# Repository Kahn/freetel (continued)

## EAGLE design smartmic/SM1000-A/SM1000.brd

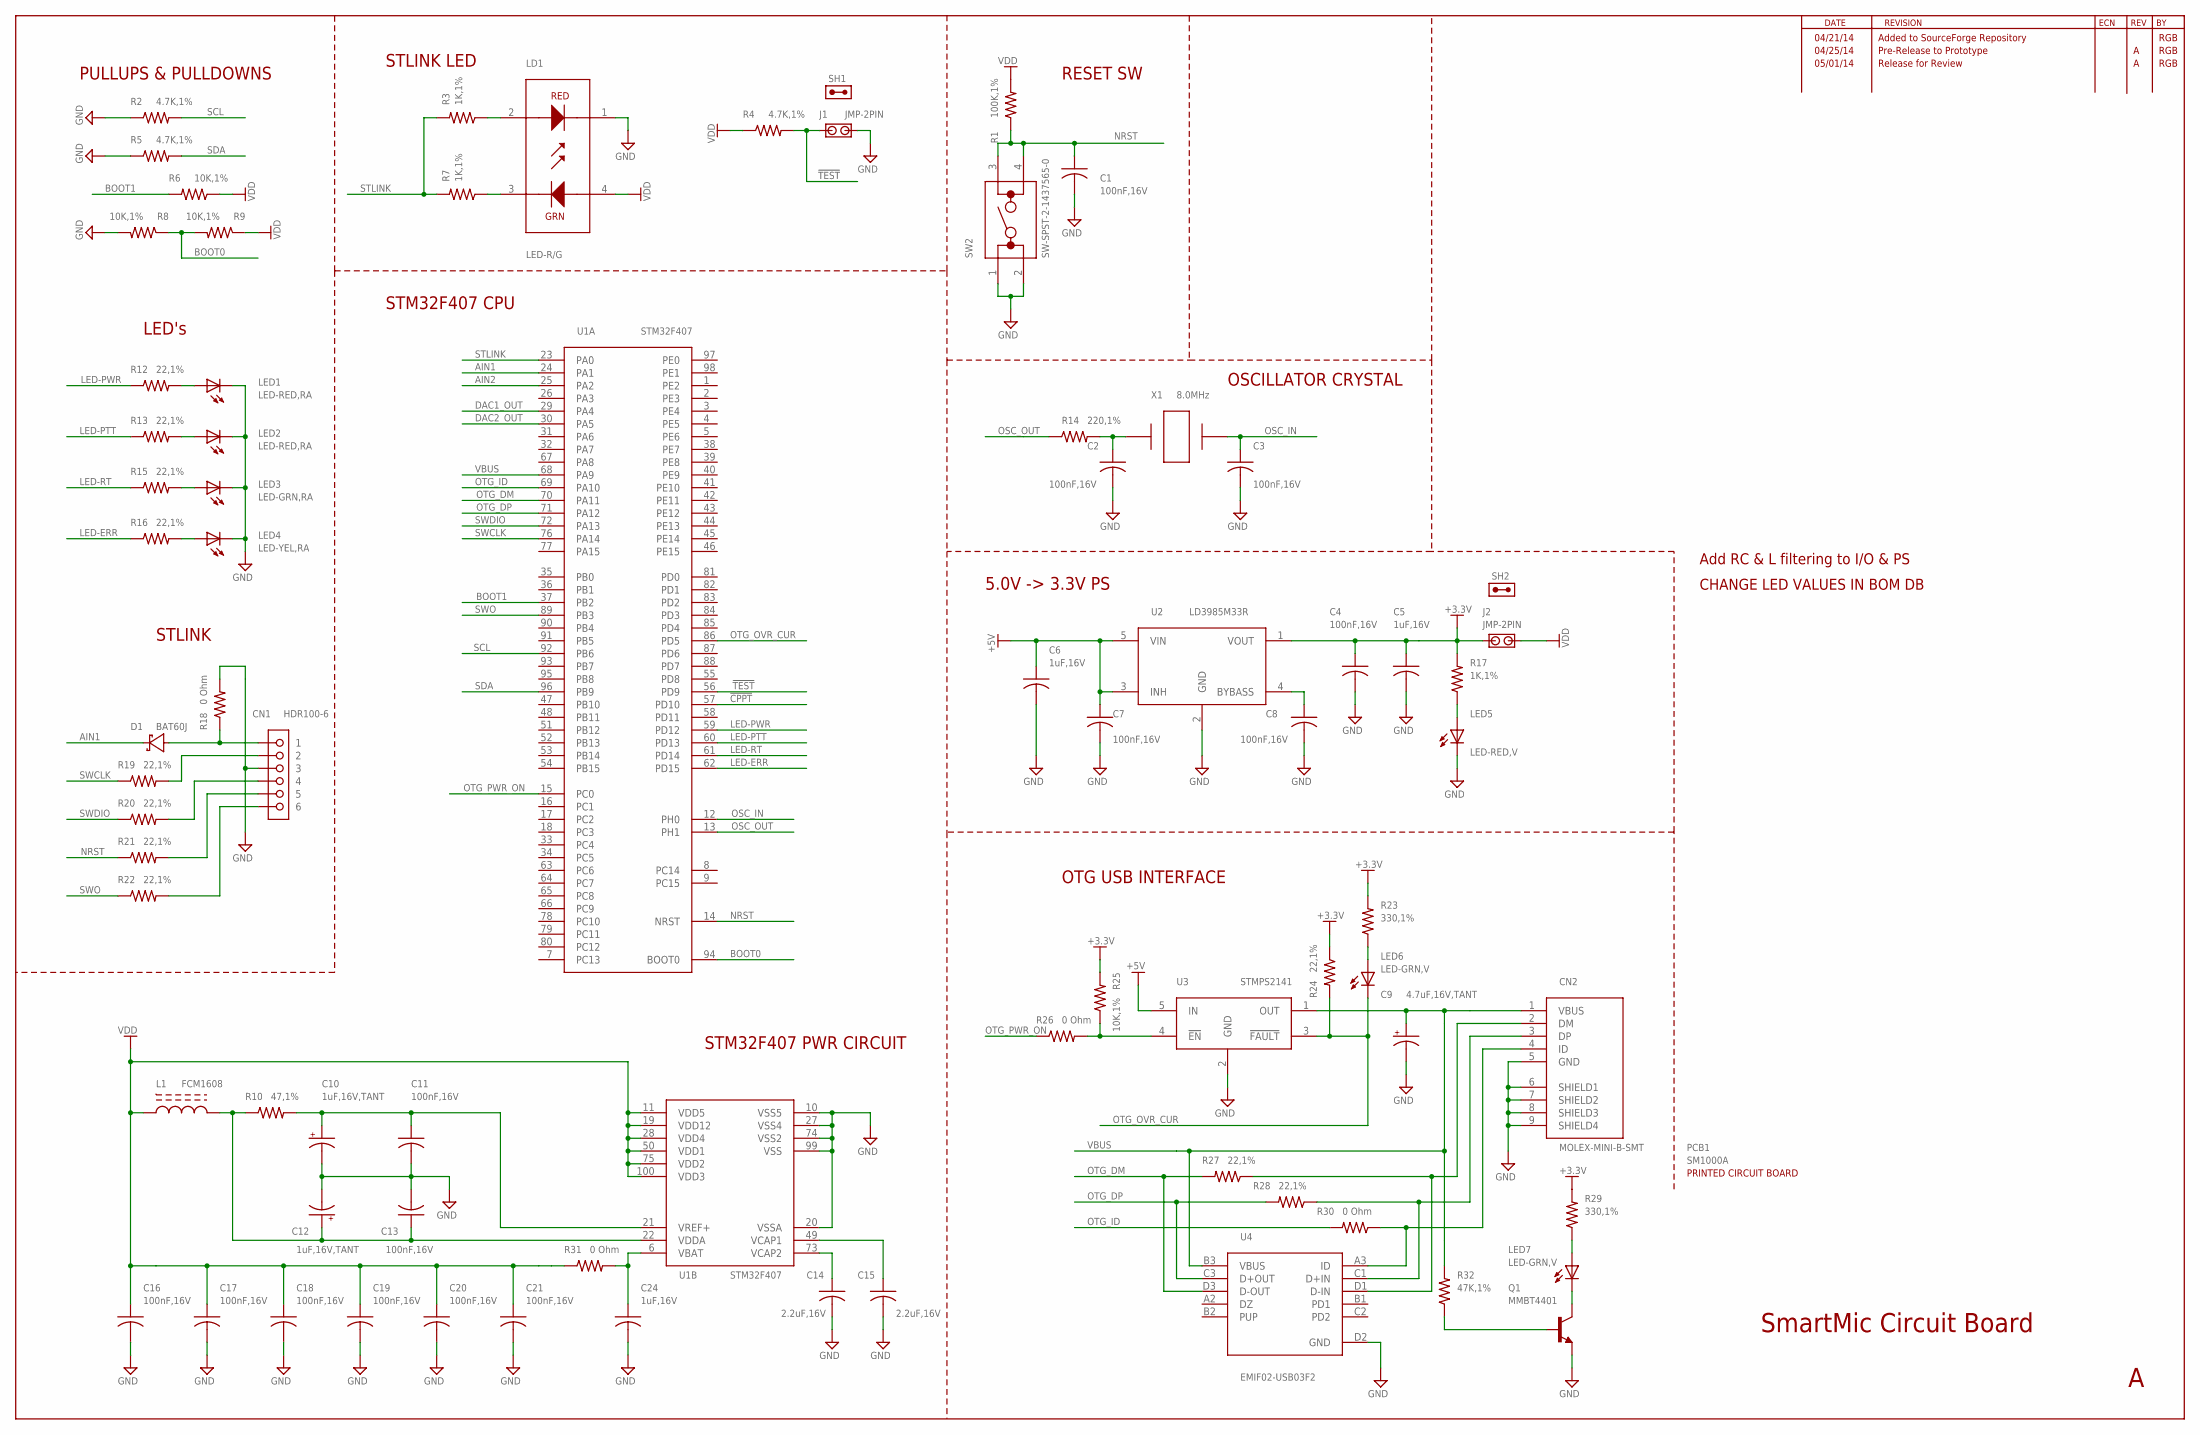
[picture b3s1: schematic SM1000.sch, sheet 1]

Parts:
C1, C2, C3, C4, C7, C8, C11, C13, C16, C17, C18, C19, C20, C21: 100nF,16V; C0603
C5, C6, C24: 1uF,16V; C0603
C9: 4.7uF,16V,TANT; C1206-TANT
C10, C12: 1uF,16V,TANT; C1206-TANT
C14, C15: 2.2uF,16V; C0805
CN1: HDR100-6
CN2: MOLEX-MINI-B-SMT
D1: BAT60J; SOD323R_INFINEON
J1, J2: JMP-2PIN; JMPR-2PIN
L1: FCM1608
LD1: LED-R/G
LED1, LED2: LED-RED,RA; LTST-S2200K
LED3: LED-GRN,RA; LTST-S2200K
LED4: LED-YEL,RA; LTST-S2200K
LED5: LED-RED,V; CHIP-LED-0603
LED6, LED7: LED-GRN,V; CHIP-LED-0603
PCB1: SM1000A; NOPACKAGE
Q1: MMBT4401; SOT23
R1: 100K,1%; R0603
R2, R4, R5: 4.7K,1%; R0603
R3, R7, R17: 1K,1%; R0603
R6, R8, R9, R25: 10K,1%; R0603
R10: 47,1%; R0603
R12, R13, R15, R16, R19, R20, R21, R22, R24, R27, R28: 22,1%; R0603
R14: 220,1%; R0603
R18, R26, R30, R31: 0 Ohm; R0603
R23, R29: 330,1%; R0603
R32: 47K,1%; R0603
SH1, SH2: SHUNT,0.1IN; NOPACKAGE
SW2: SW-SPST-2-1437565-0; SW-SPST-TE-2-1437565-0
U1: STM32F407; LQFP100-14
U2: LD3985M33R; SOT23-5L
U3: STMPS2141; SOT23-5L
U4: EMIF02-USB03F2; ECOPACK-11
X1: 8.0MHz; HC49-SMT

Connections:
!CPPT!: U1.57 (PD10); also elsewhere on the board
!TEST!: J1.1, R4.2, U1.56 (PD9)
+3.3V: C4.1, C5.1, J2.1, R17.2, R23.2, R24.1, R25.2, R29.2, U2.1 (VOUT)
+5V: C6.1, C7.1, U2.3 (INH), U2.5 (VIN), U3.5 (IN); also elsewhere on the board
AIN1: D1.C, U1.24 (PA1)
AIN2: U1.25 (PA2); also elsewhere on the board
BOOT0: R8.1, R9.2, U1.94 (BOOT0)
BOOT1: R6.2, U1.37 (PB2)
DAC1_OUT: U1.29 (PA4); also elsewhere on the board
DAC2_OUT: U1.30 (PA5); also elsewhere on the board
GND: C1.2, C2.2, C3.2, C4.2, C5.2, C6.2, C7.2, C8.2, C9.2, C10.2, C11.2, C12.2, C13.2, C14.2, C15.2, C16.2, C17.2, C18.2, C19.2, C20.2, C21.2, C24.2, CN1.3, CN2.5 (GND), CN2.6 (SHIELD1), CN2.7 (SHIELD2), CN2.8 (SHIELD3), CN2.9 (SHIELD4), J1.2, LD1.1, LED1.C, LED2.C, LED3.C, LED4.C, LED5.C, Q1.2 (E), R2.1, R5.1, R8.2, R18.2, SW2.1, SW2.2, U1.10 (VSS5), U1.20 (VSSA), U1.27 (VSS4), U1.74 (VSS2), U1.99 (VSS), U2.2 (GND), U3.2 (GND), U4.D2 (GND); also elsewhere on the board
LED-ERR: R16.1, U1.62 (PD15)
LED-PTT: R13.1, U1.60 (PD13)
LED-PWR: R12.1, U1.59 (PD12)
LED-RT: R15.1, U1.61 (PD14)
unnamed: C14.1, U1.73 (VCAP2)
unnamed: C24.1, R31.2, U1.6 (VBAT)
unnamed: C15.1, U1.49 (VCAP1)
unnamed: C10.1, C11.1, R10.2, U1.21 (VREF+)
unnamed: C12.1, C13.1, L1.2, R10.1, U1.22 (VDDA)
unnamed: CN1.1, D1.A, R18.1
unnamed: CN1.2, R19.2
unnamed: CN1.4, R20.2
unnamed: CN1.5, R21.2
unnamed: C2.1, R14.2, X1.1
unnamed: CN1.6, R22.2
unnamed: C8.1, U2.4 (BYBASS)
unnamed: LD1.2, R3.1
unnamed: LD1.3, R7.1
unnamed: Q1.1 (B), R32.1
unnamed: LED1.A, R12.2
unnamed: LED2.A, R13.2
unnamed: LED3.A, R15.2
unnamed: LED5.A, R17.1
unnamed: LED4.A, R16.2
unnamed: CN2.3 (DP), R28.1, U4.C1 (D+IN)
unnamed: CN2.2 (DM), R27.1, U4.D1 (D-IN)
unnamed: LED7.C, Q1.3 (C)
unnamed: LED7.A, R29.1
unnamed: CN2.4 (ID), R30.1, U4.A3 (ID)
unnamed: LED6.A, R23.1
unnamed: R25.1, R26.2, U3.4 (!EN!)
NRST: C1.1, R1.1, R21.1, SW2.3, SW2.4, U1.14 (NRST)
OSC_IN: C3.1, U1.12 (PH0), X1.2
OSC_OUT: R14.1, U1.13 (PH1)
OTG_DM: R27.2, U1.70 (PA11), U4.D3 (D-OUT)
OTG_DP: R28.2, U1.71 (PA12), U4.C3 (D+OUT)
OTG_ID: R30.2, U1.69 (PA10)
OTG_OVR_CUR: LED6.C, R24.2, U1.86 (PD5), U3.3 (!FAULT!)
OTG_PWR_ON: R26.1, U1.15 (PC0)
SCL: R2.2, U1.92 (PB6)
SDA: R5.2, U1.96 (PB9)
STLINK: R3.2, R7.2, U1.23 (PA0)
SWCLK: R19.1, U1.76 (PA14)
SWDIO: R20.1, U1.72 (PA13)
SWO: R22.1, U1.89 (PB3)
VBUS: C9.1, CN2.1 (VBUS), R32.2, U1.68 (PA9), U3.1 (OUT), U4.B3 (VBUS)
VDD: C16.1, C17.1, C18.1, C19.1, C20.1, C21.1, J2.2, L1.1, LD1.4, R1.2, R4.1, R6.1, R9.1, R31.1, U1.11 (VDD5), U1.19 (VDD12), U1.28 (VDD4), U1.50 (VDD1), U1.75 (VDD2), U1.100 (VDD3); also elsewhere on the board

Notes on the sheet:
PULLUPS & PULLDOWNS
LED's
STLINK
STLINK LED
RESET SW
OSCILLATOR CRYSTAL
5.0V -> 3.3V PS
OTG USB INTERFACE
STM32F407 CPU
STM32F407 PWR CIRCUIT
SmartMic Circuit Board
04/21/14
Added to SourceForge Repository
RGB
CHANGE LED VALUES IN BOM DB
Add RC & L filtering to I/O & PS
04/25/14
Pre-Release to Prototype
05/01/14
Release for Review

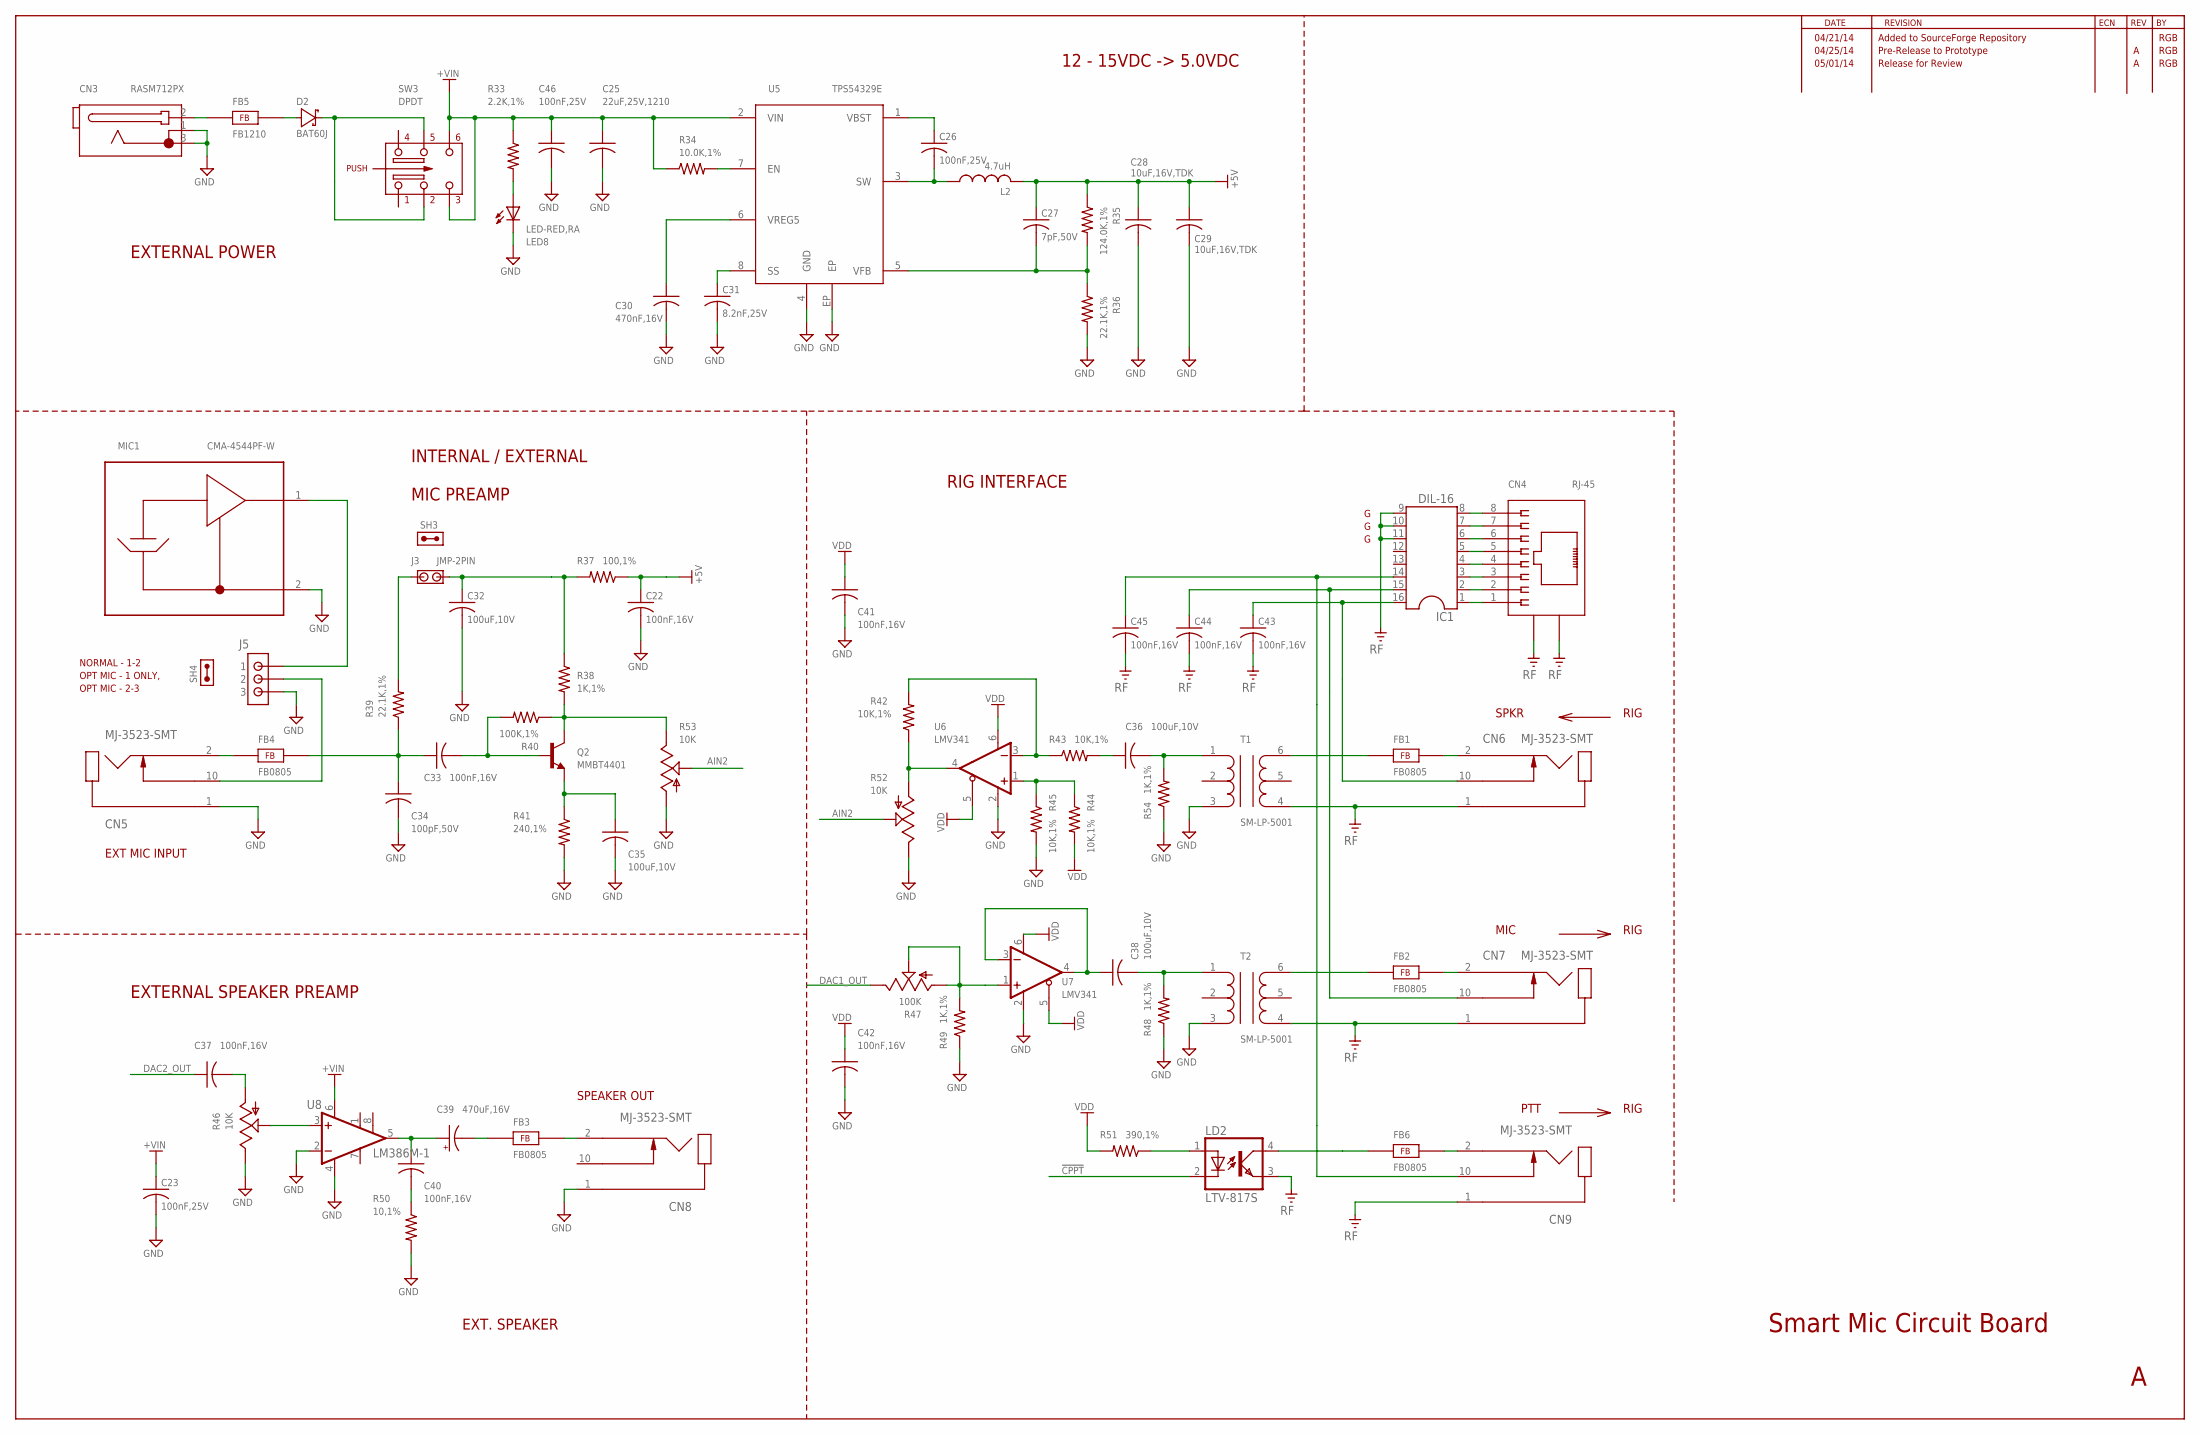
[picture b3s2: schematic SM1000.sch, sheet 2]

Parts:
C22, C33, C37, C40, C41, C42, C43, C44, C45: 100nF,16V; C0603
C23, C26, C46: 100nF,25V; C0603
C25: 22uF,25V,1210; C1210
C27: 7pF,50V; C0603
C28, C29: 10uF,16V,TDK; C1206
C30: 470nF,16V; C0603
C31: 8.2nF,25V; C0603
C32, C35, C36, C38: 100uF,10V; C1210
C34: 100pF,50V; C0603
C39: 470uF,16V; CAP-CHEMI-HA0
CN3: RASM712PX
CN4: RJ-45; CONN-RJ45-MOLEX-44144-003
CN5, CN6, CN7, CN8, CN9: MJ-3523-SMT
D2: BAT60J; SOD323R_INFINEON
FB1, FB2, FB3, FB4, FB6: FB0805; FE0805
FB5: FB1210; FE1210
IC1: DIL-16; SOCKET-16
J3: JMP-2PIN; JMPR-2PIN
J5: JMPR-3PIN
L2: 4.7uH; SRN6045
LD2: LTV-817S; SMD4
LED8: LED-RED,RA; LTST-S2200K
MIC1: CMA-4544PF-W
Q2: MMBT4401; SOT23
R33: 2.2K,1%; R0603
R34: 10.0K,1%; R0603
R35: 124.0K,1%; R0603
R36, R39: 22.1K,1%; R0603
R37: 100,1%; R0603
R38, R48, R49, R54: 1K,1%; R0603
R40: 100K,1%; R0603
R41: 240,1%; R0603
R42, R43, R44, R45: 10K,1%; R0603
R46: 10K; POT-3310C
R47: 100K; TRIMPOT91
R50: 10,1%; R0603
R51: 390,1%; R0603
R52, R53: 10K; TRIMPOT91
SH3, SH4: SHUNT,0.1IN; NOPACKAGE
SW3: DPDT; SW-PWR
T1, T2: SM-LP-5001
U5: TPS54329E; PSO-DDA
U6, U7: LMV341; SOT23-6
U8: LM386M-1; SO08

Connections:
!CPPT!: LD2.2 (C); also elsewhere on the board
+5V: C22.1, C27.1, C28.1, C29.1, L2.2, R35.1, R37.1; also elsewhere on the board
+VIN: C23.1, C25.1, C46.1, R33.1, R34.1, SW3.3, SW3.6, U5.2 (VIN), U8.6 (VS)
AIN2: R52.2, R53.2; also elsewhere on the board
DAC1_OUT: R47.1; also elsewhere on the board
DAC2_OUT: C37.1; also elsewhere on the board
GND: C22.2, C23.2, C25.2, C28.2, C29.2, C30.2, C31.2, C32.2, C34.2, C35.2, C41.2, C42.2, C46.2, CN3.1, CN3.3, CN5.1, CN8.1, J5.3, LED8.C, MIC1.2, R36.2, R41.2, R45.2, R46.1, R48.1, R49.1, R50.2, R52.1, R53.3, R54.1, T1.3, T2.3, U5.4 (GND), U5.EP, U6.2 (GND), U7.2 (GND), U8.2 (-IN), U8.4 (GND); also elsewhere on the board
MIC: C44.1, CN7.10, IC1.15
unnamed: C26.1, U5.1 (VBST)
unnamed: D2.A, FB5.2
unnamed: C33.1, C34.1, FB4.2, R39.1
unnamed: C27.2, R35.2, R36.1, U5.5 (VFB)
unnamed: J5.1, MIC1.1
unnamed: FB1.1, T1.6
unnamed: C37.2, R46.3
unnamed: C33.2, Q2.1 (B), R40.2
unnamed: C39.1, C40.1, U8.5 (OUT)
unnamed: C31.1, U5.8 (SS)
unnamed: R46.2, U8.3 (+IN)
unnamed: C30.1, U5.6 (VREG5)
unnamed: C35.1, Q2.2 (E), R41.1
unnamed: R34.2, U5.7 (EN)
unnamed: C40.2, R50.1
unnamed: C39.2, FB3.1
unnamed: J3.1, R39.2
unnamed: C32.1, J3.2, R37.2, R38.1
unnamed: LED8.A, R33.2
unnamed: R42.1, R52.3, U6.4 (OUT)
unnamed: LD2.1 (A), R51.1
unnamed: C36.1, R43.2
unnamed: CN4.8, IC1.8
unnamed: CN4.7, IC1.7
unnamed: CN4.6, IC1.6
unnamed: CN4.5, IC1.5
unnamed: CN4.4, IC1.4
unnamed: CN4.3, IC1.3
unnamed: CN4.2, IC1.2
unnamed: CN4.1, IC1.1
unnamed: R44.1, R45.1, U6.1 (+IN)
unnamed: CN5.10, J5.2
unnamed: FB2.1, T2.6
unnamed: R42.2, R43.1, U6.3 (-IN)
unnamed: C36.2, R54.2, T1.1
unnamed: CN6.2, FB1.2
unnamed: C38.2, R48.2, T2.1
unnamed: Q2.3 (C), R38.2, R40.1, R53.1
unnamed: C38.1, U7.3 (-IN), U7.4 (OUT)
unnamed: CN7.2, FB2.2
unnamed: CN9.2, FB6.2
unnamed: FB6.1, LD2.4 (COL)
unnamed: CN8.2, FB3.2
unnamed: CN5.2, FB4.1
unnamed: CN3.2, FB5.1
unnamed: D2.C, SW3.2, SW3.5
unnamed: R47.2, R47.3, R49.2, U7.1 (+IN)
PTT: C45.1, CN9.10, IC1.14
RF: C43.2, C44.2, C45.2, CN4.9, CN4.10, CN6.1, CN7.1, CN9.1, IC1.9, IC1.10, IC1.11, LD2.3 (EMIT), T1.4, T2.4
SPKR: C43.1, CN6.10, IC1.16
SW: C26.2, L2.1, U5.3 (SW)
VDD: C41.1, C42.1, R44.2, R51.2, U6.5 (!SHDN!), U6.6 (V+), U7.5 (!SHDN!), U7.6 (V+); also elsewhere on the board

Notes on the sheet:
SPKR
MIC
RIG
SPEAKER OUT
PTT
EXT MIC INPUT
EXTERNAL POWER
12 - 15VDC -> 5.0VDC
INTERNAL / EXTERNAL
MIC PREAMP
EXTERNAL SPEAKER PREAMP
RIG INTERFACE
Smart Mic Circuit Board
EXT. SPEAKER
NORMAL - 1-2
OPT MIC - 1 ONLY,
OPT MIC - 2-3
04/25/14
Pre-Release to Prototype
RGB
04/21/14
Added to SourceForge Repository
05/01/14
Release for Review

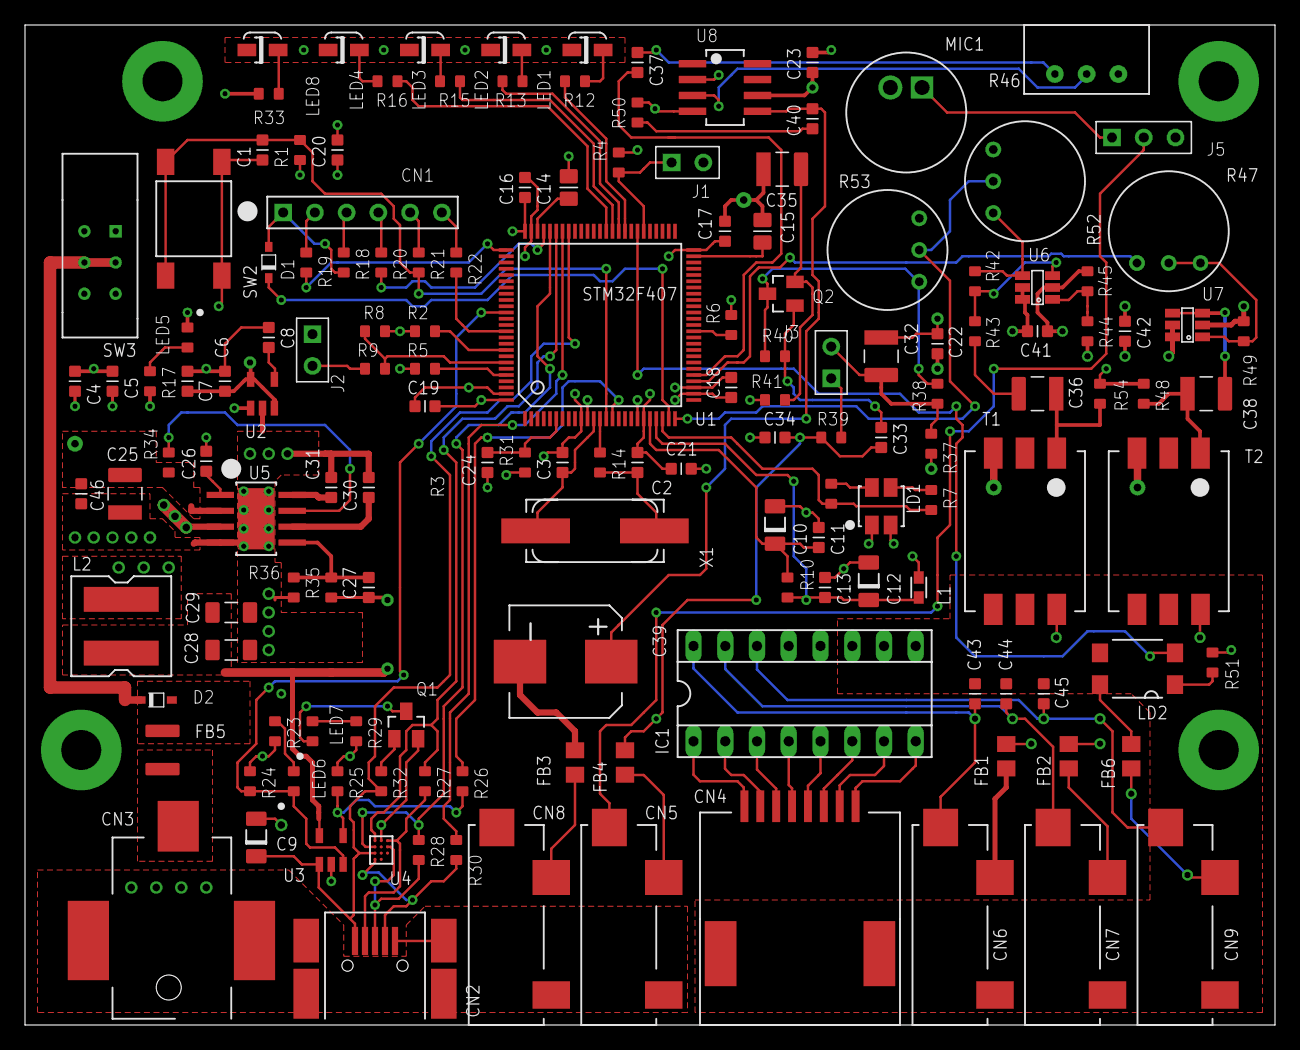
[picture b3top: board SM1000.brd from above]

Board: 4 copper layers, 100.0 x 80.0 mm, 155 parts (0 on the bottom side), 111 nets.

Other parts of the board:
DRILEGEND: DRILEGEND

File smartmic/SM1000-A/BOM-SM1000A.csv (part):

"Bill of Materials from SM1000.sch, 154 parts, grouped by values, as of 5/1/2014 3:17:26 PM"
"Part","Qty","DEFINITION","MANUFACTURER","MFG_NUMBER","DISTRIBUTOR","DIST_NUMBER","GENERIC","ROHS","COST100",
"C1, C2, C3, C4, C7, C8, C11, C13, C16, C17, C18, C19, C20, C21, C22, C33, C37, C40, C41, C42, C43, C44, C45","23","CAP CER 0.1UF 16V 10% X7R 0603","YAGEO","CC0603KRX7R7BB104","DIGIKEY","311-1088-1-ND","Y","Y","0.013"
"C5, C6, C24","3","CAP CER 1UF 16V 10% X5R 0603","TDK","C1608X5R1C105K080AA","DIGIKEY","445-1416-1-ND","Y","Y","0.034"
"C9","1","CAP TANT 4.7UF 16V 10% 1206","AVX","TAJA475K016RNJ","DIGIKEY","478-3868-1-ND","Y","Y","0.260"
"C10, C12","2","CAP TANT 1UF 16V 20% 1206","NICHICON","F931C105MAA","DIGIKEY","493-2364-1-ND","Y","Y","0.152"
"C14, C15","2","CAP CER 2.2UF 16V Y5V 0805","YAGEO","CC0805ZRY5V7BB225","DIGIKEY","311-1463-1-ND","Y","Y","0.042"
"C23, C26, C46","3","CAP CER 0.1UF 16V 10% X7R 0603","YAGEO","CC0603KRX7R7BB104","DIGIKEY","311-1088-1-ND","Y","Y","0.013"
"C25","1","CAP CER 22UF 25V 10% X5R 1210","MURATA","GRM32ER61E226KE15L","DIGIKEY","490-3889-1-ND","N","Y","0.540"
"C27","1","CAP CER 7PF 50V NPO 0603","YAGEO","CC0603DRNPO9BN7R0","DIGIKEY","311-1056-1-ND","N","Y","0.029"
"C28, C29","2","CAP CER 10UF 10V 20% X5R 1206","TDK","C3216X5R1A106M160AB","DIGIKEY","445-1387-1-ND","N","Y","0.114"
"C30","1","CAP CER 0.47UF 16V 10% X5R 0603","TDK","C1608X5R1C474K080AA","DIGIKEY","445-5152-1-ND","N","Y","0.030"
"C31","1","CAP CER 0.082UF 25V 10% X7R 0603","MURATA","GRM188R71E823KA01D","DIGIKEY","490-6434-1-ND","N","Y","0.050"
"C32, C35, C36, C38","4","CAP CER 100UF 10V 20% X5R 1210","SAMSUNG","CL32A107MPVNNNE","DIGIKEY","1276-3364-1-ND","Y","Y","0.735"
"C34","1","CAP CER 100PF 50V 5% NP0 0603","TDK","C1608NP01H101J080AA","DIGIKEY","445-14054-1-ND","Y","Y","0.038"
"C39","1","CAP ALUM 470UF 16V 20% SMD","UNITED CHEMI-CON","EMVE160ADA471MHA0G","DIGIKEY","565-2208-1-ND","Y","Y","0.456"
"CN1","1","CONN HEADER 6POS .100 VERT GOLD","MOLEX","22-10-2061","DIGIKEY","WM2726-ND","Y","Y","0.985"
"CN2","1","CONN RECEPT MINIUSB R/A 5POS SMD","MOLEX","0675031020","DIGIKEY","WM5461CT-ND","N","Y","0.856"
"CN3","1","CONN JACK R/A .100" PIN SMD","SWITCHCRAFT","RASM712PX","DIGIKEY","RASM712PX-ND","N","Y","1.082"
"CN4","1","CONN MOD JACK R/A 8P8C","MOLEX","0441440003","DIGIKEY","WM4595CT-ND","N","Y","1.387"
"CN5, CN6, CN7, CN8, CN9","5","CONN AUDIO JACK MONO 3.5MM SMD","CUI","MJ-3523-SMT-TR","DIGIKEY","CP-3523MJTR-ND","N","Y","0.796"
"D1, D2","2","DIODE SCHOTTKY 10V 3A SOD323","STM","BAT60JFILM","DIGIKEY","497-3707-1-ND","Y","Y","0.240"
"FB1, FB2, FB3, FB4, FB6","5","FERRITE 500MA 600 OHM 0805 SMD","lAIRD","HZ0805E601R-10","DIGIKEY","240-2399-1-ND","N","Y","0.0381"
"FB5","1","FERRITE 1.5A 60 OHM 1210 SMD","LAIRD","MI1210K600R-10","DIGIKEY","240-2416-1-ND","N","Y","0.100"
"IC1","1","CONN SOCKET IC 16-PIN T/H","ON SHORE TECHNOLOGY","SA163040","DIGIKEY","ED3017-ND","Y","Y"," "
"J1, J2, J3","3","CONN HEADER 2POS .100 VERT GOLD","MOLEX","22-28-4023","DIJIKEY","WM6502-ND","Y","Y","0.190"
"J5","1","CONN HEADER 3POS .100 VERT GOLD","MOLEX","22-28-4033","DIGIKEY","WM6503-ND","Y","Y",".18"
"L1","1","FERRITE CHIP 120 OHM 2000MA 0603","MURATA","BLM18PG121SN1D","DIGIKEY","490-1037-1-ND","N","Y","0.050"
"L2","1","INDUCTOR POWER SHIELD 4.7UH SMD","BOURNS","SRN6045-4R7Y","DIGIKEY","SRN6045-4R7YCT-ND","N","Y","0.270"
"LD1","1","LED IND RED/GRN TOP MOUNT 4PLCC","AVAGO","HSMF-A201-A00J1","DIGIKEY","516-2491-1-ND","N","Y","0.341"
"LD2","1","OPTOISOLATR 5KV TRANSISTOR 4-SMD","LITE-ON","LTV-817S-TA1","DIGIKEY","160-1893-1-ND","N","Y","0.217"
"LED1, LED2, LED8","3","LED SUPR RED CLR RT ANG 0805","LITE-ON","LTST-S220KRKT","DIGIKEY","160-1469-1-ND","Y","Y","0.1151"
"LED3","1","LED GREEN CLEAR RT ANG 0805","LITE-ON","LTST-S220KGKT","DIGIKEY","160-1468-1-ND","N","Y","0.135"
"LED4","1","LED YELLOW CLEAR RT ANG 0805","LITE-ON","LTST-S220KSKT","DIGIKEY","160-1470-1-ND","N","Y","0.143"
"LED5","1","LED 660NM SUPER RED DIFF 0603SMD","LITE-ON","SML-LX0603SRW-TR","DIGIKEY","67-1551-1-ND","Y","Y","0.169"
"LED6, LED7","2","LED ALINGAP GRN WHT DIFF 0603SMD","LITE-ON","SML-LX0603GW-TR","DIGIKEY","67-1549-1-ND","Y","Y","0.196"
"MIC1","1","MIC COND ANALOG OMNI -44DB","CUI","CMA-4544PF-W","DIGIKEY","102-1721-ND","N","Y","0.569"
"PCB1","1","PCB-SM1000, REV-A","?","?","PCB UNIVERSE","SM1000A","N","Y","5.76"
"Q1, Q2","2","TRANSISTOR NPN GP 40V SOT23","Micro Commercial Co","MMBT4401-TP","DIGIKEY","MMBT4401TPMSCT-ND","Y","Y","0.110"
"R1, R40","2","RES 100K OHM 1/10W 1% 0603 SMD","VISHAY/DALE","CRCW0603100KFKEA","DIGIKEY","541-100KHCT-ND","Y","Y","0.025"
"R2, R4, R5","3","RES 4.70K OHM 1/10W 1% 0603 SMD","VISHAY-DALE","CRCW06034K70FKEA","DIGIKEY","541-4.70KHCT-ND","Y","Y","0.025"
"R3, R7, R17, R38, R48, R49, R54","7","RES 1.00K OHM 1/10W 1% 0603 SMD","VISHAY-DALE","CRCW06031K00FKEA","DIGIKEY","541-1.00KHCT-ND","Y","Y","0.025"
"R6, R8, R9, R25, R42, R43, R44, R45","8","RES 10.0K OHM 1/10W 1% 0603 SMD","VISHAY/DALE","CRCW060310K0FKEA","DIGIKEY","541-10.0KHCT-ND","Y","Y","0.025"
"R10","1","RES 47.0 OHM 1/10W 1% 0603 SMD","VISHAY-DALE","CRCW060347R0FKEA","DIGIKEY","541-47.0HCT-ND","Y","Y","0.025"
"R12, R13, R15, R16, R19, R20, R21, R22, R24, R27, R28","11","RES 22.0 OHM 1/10W 1% 0603 SMD","VISHAY-DALE","CRCW060322R0FKEA","DIGIKEY","541-22.0HCT-ND","Y","Y","0.025"
"R14","1","RES 220 OHM 1/10W 1% 0603 SMD","VISHAY DALE","CRCW0603220RFKEA","DIGIKEY","541-220HCT-ND","Y","Y"," "
"R18, R26, R30, R31","4","RES 0.0 OHM 1/10W JUMP 0603 SMD","VISHAY-DALE","CRCW06030000Z0EA","DIGIKEY","541-0.0GCT-ND","Y","Y","0.023"
"R23, R29","2","RES 330 OHM 1/10W 1% 0603 SMD","VISHAY-DALE","CRCW0603330RFKEA","DIGIKEY","541-330HCT-ND","Y","Y","0.025"
"R32","1","RES 47.0K OHM 1/10W 1% 0603 SMD","VISHAY-DALE","CRCW060347K0FKEA","DIGIKEY","541-47.0KHCT-ND","G","Y","0.025"
"R33","1","RES 2.20K OHM 1/10W 1% 0603 SMD","VISHAY-DALE","CRCW06032K20FKEA","DIGIKEY","541-2.20KHDKR-ND","Y","Y","0.030"
"R34","1","RES 10.0K OHM 1/10W 1% 0603 SMD","VISHAY-DALE","CRCW060310K0FKEA","DIGIKEY","541-10.0KHCT-ND","Y","Y","0.025"
"R35","1","RES 124K OHM 1/10W 1% 0603 SMD","VISHAY-DALE","CRCW0603124KFKEA","DIGIKEY","541-124KHCT-ND","Y","Y","0.025"
"R36, R39","2","RES 22.1K OHM 1/10W 1% 0603 SMD","VISHAY-DALE","CRCW060322K1FKEA","DIGIKEY","541-22.1KHCT-ND","Y","Y","0.025"
"R37","1","RES 100 OHM 1/10W 1% 0603 SMD","VISHAY-DALE","CRCW0603100RFKEA","DIGIKEY","541-100HCT-ND","Y","Y","0.025"
"R41","1","RES 240 OHM 1/10W 1% 0603 SMD","VISHAY-DALE","CRCW0603240RFKEA","DIGIKEY","541-240HCT-ND","Y","Y","0.025"
"R46","1","RES 10K OHM 1/8W 5% 0805 SMD","VISHAY/DALE","CRCW080510K0JNEA","DIGIKEY","541-10KACT-ND","Y","Y","0.033"
"R47","1","RES 100K OHM 1/8W 5% 0805 SMD","VISHAY/DALE","CRCW0805100KJNEA","DIGIKEY","541-100KACT-ND","Y","Y",".024"
"R50","1","RES 10.0 OHM 1/10W 1% 0603 SMD","VISHAY-DALE","CRCW060310R0FKEA","DIGIKEY","541-10.0HCT-ND","Y","Y","0.025"
"R51","1","RES 390 OHM 1/10W 1% 0603 SMD","VISHAY-DALE","CRCW0603390RFKEA","DIGIKEY","541-390HCT-ND","Y","Y","0.025"
"R52, R53","2","RES 10K OHM 1/8W 5% 0805 SMD","VISHAY/DALE","CRCW080510K0JNEA","DIGIKEY","541-10KACT-ND","Y","Y","0.033"
"SH1, SH2, SH3, SH4","4","SHUNT LP 2 POS SN","TYCO AMP","1-382811-6","DIGIKEY","A26231-ND","Y","Y","0.210"
"SW2","1","SWITCH TACTILE SPST-NO 0.05A 12V","TE","FSM2JSMATR","DIGIKEY","450-1757-1-ND","N","Y","0.211"
"SW3","1","SWITCH PUSH DPDT 0.1A 30V","E-SWITCH","PBH2UEENAGX","DIGIKEY","EG2655-ND","N","Y","1.332"
"T1, T2","2","TRANSF LINE MATCHING SMD","BOURNS","SM-LP-5001E","DIGIKEY","SM-LP-5001ECT-ND","N","Y","1.506"
"U1","1","IC MCU 32BIT 1MB FLASH 100LQFP","STM","STM32F407VGT6","DIGIKEY","497-11605-ND","N","Y","9.878"
"U2","1","IC REG LDO 3.3V 0.15A SOT23-5","STM","LD3985M33R","DIGIKEY","497-3504-1-ND","N","Y","0.466"
"U3","1","IC PWR SWITCH 1CH 500MA SOT23-5","STM","STMPS2141STR","DIGIKEY","497-6933-1-ND","N","Y","0.480"
"U4","1","I C EMI FILTR/ESD PROT 11FLIPCHIP","STM","EMIF02-USB03F2","DIGIKEY","497-13521-1-ND","N","Y","0.525"
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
